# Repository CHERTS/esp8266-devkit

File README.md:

Unofficial Development Kit for Espressif ESP8266
================================================

[По-русски / In Russian](README.ru.md)

<b>Unofficial Development Kit for Espressif ESP8266</b> - this is an unofficial firmware development kit for SoC Espressif ESP8266.<br>

<b>The kit includes the following components and tools:</b><br>

1. Unofficial GCC compiler for SoC Xtensa LX106.<br>
2. Official Espressif ESP8266 SDK v2.0.0<br>
3. Documentation for SoC ESP8266.<br>
4. Examples in the firmware source code in C and С++ language.<br>
5. Additional tools for working with boards based on the ESP8266.<br>

<a href="http://programs74.ru/udkew-en.html">Official site of the project, where you can download the installer for Windows</a>

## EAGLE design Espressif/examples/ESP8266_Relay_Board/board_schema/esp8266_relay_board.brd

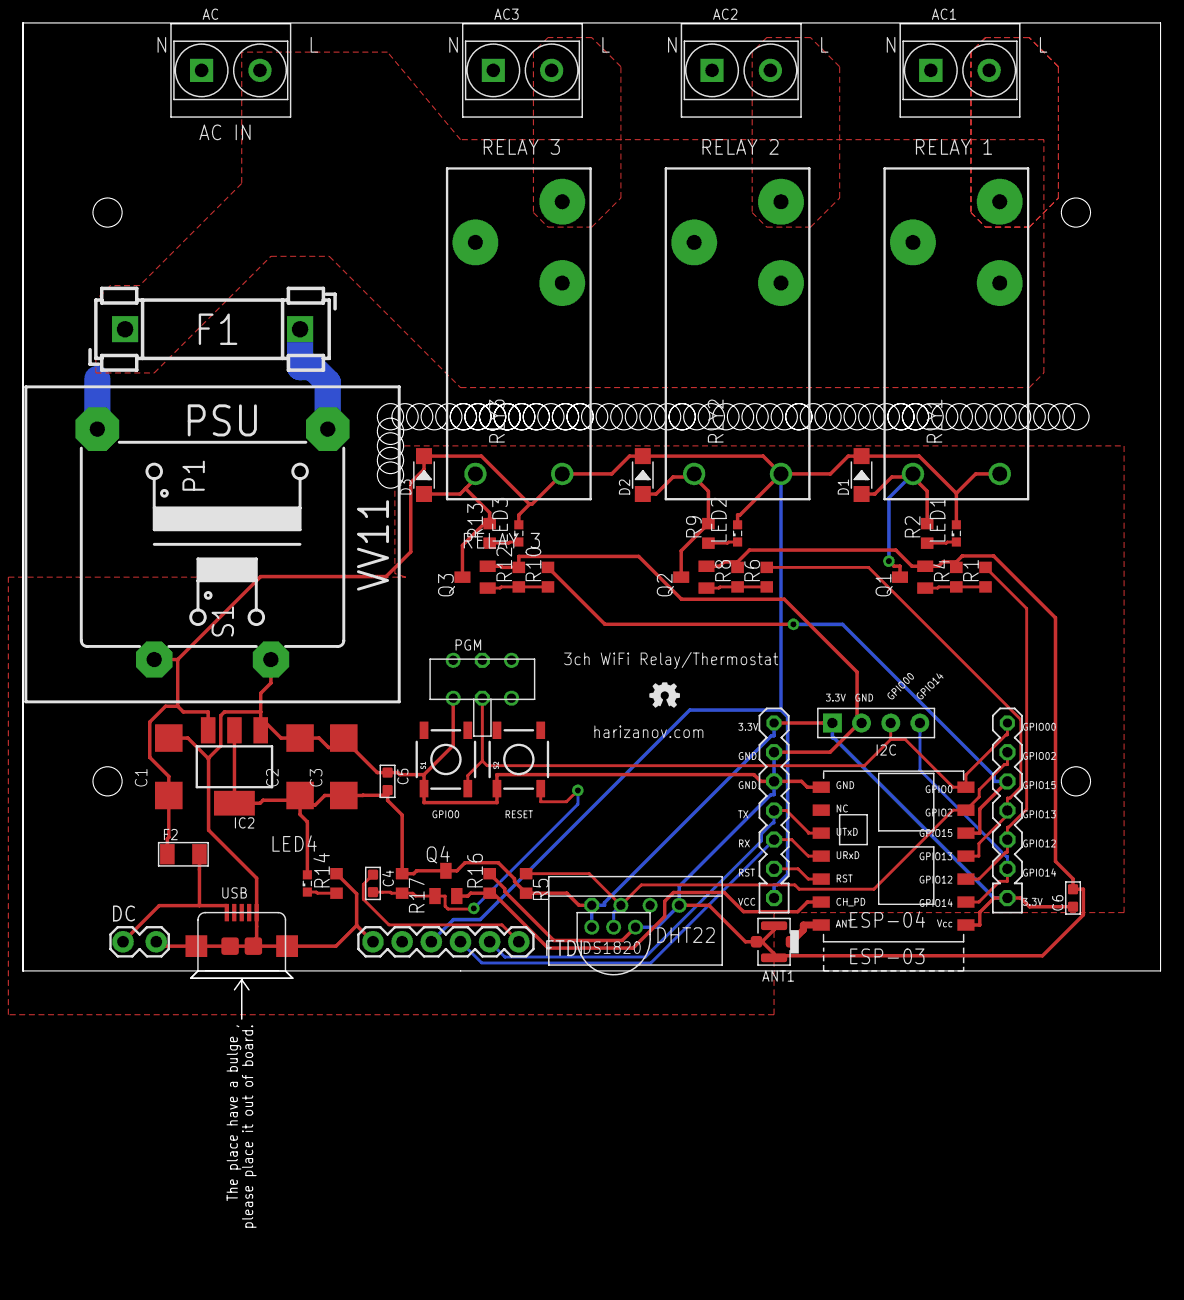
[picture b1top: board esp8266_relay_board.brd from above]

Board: 2 copper layers, 99.1 x 86.7 mm, 54 parts (0 on the bottom side), 33 nets.

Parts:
AC, AC1, AC2, AC3: 2P-5.0
ANT1: U-FL
C1: 10u/35V; SMC_C
C2, C3: 470uF/35V; SMC_C
C4, C5, C6: 100nF; C0603
D1, D2, D3: SOD-123
DC: 1X02_LOCK
DHT22: RHT03_DHT-22
ESP8266: ESP8266; ESP-04
F1: FUSE_HOLDER_5X20MM
F2: F1206
FTDI: FTDI_BASIC
I2C: 4P-2.54-65/35MIL
IC2: LM1117-IMP3.3; SOT223
LED1, LED2, LED3, LED4: SML0603
PGM: 6P-2CH-2.54-L9.0XW3.5XH3.2-90D
PORT5, PORT11: CON7PIN-PAD; PORT7PAD
PSU: VV11
Q1, Q2, Q3, Q4: 2N3904; SOT23
R1, R2, R6, R9, R10, R13, R14, R16: 330; R0603
R4, R8, R12: 3.3K; R0603
R5, R17: 10K; R0603
RLY1, RLY2, RLY3: RT-C/O12A3.5
S1, S2: !RESET; TACTILE_SWITCH_SMD
U$1: DS1820TO92; DS1820
USB: B-SMD-5P

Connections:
+3V3: C2.+, C3.+, C5.2, C6.1, DHT22.VDD, ESP8266.VCC, I2C.1, IC2.2, IC2.TER, LED4.A, PORT5.7, PORT11.1, Q4.3, R5.2, R17.1, U$1.VDD
CH_PD: ESP8266.CH_PD, Q4.2, R16.1
GND: ANT1.GND1, ANT1.GND2, ANT1.GND3, C1.-, C2.-, C3.-, C5.1, C6.2, DC.2, DHT22.GND, ESP8266.GND, FTDI.GND, I2C.2, IC2.1, PGM.CH1A, PORT5.5, PORT5.6, PSU.9, Q1.2, Q2.2, Q3.2, R4.2, R8.2, R12.2, R14.2, R16.2, S1.1, S2.1, U$1.GND, USB.5, USB.E1, USB.E2, USB.P1, USB.P2
GPIO0: ESP8266.GPIO0, I2C.3, PGM.COM1, PORT11.7, S1.3
GPIO2: DHT22.DATA, ESP8266.GPIO2, PORT11.6, R5.1, U$1.DQ
GPIO12: ESP8266.GPIO12, PORT11.3, R1.2
GPIO13: ESP8266.GPIO13, PORT11.4, R6.2
GPIO14: ESP8266.GPIO14, I2C.4, PORT11.2
GPIO15: ESP8266.GPIO15, PORT11.5, R10.2
GPIO16: ESP8266.GPIO18, PORT5.2
L: AC.2, F1.1, RLY1.11, RLY1.12, RLY2.11, RLY2.12, RLY3.11, RLY3.12
LOAD2: AC1.2, RLY1.14
LOAD22: AC2.2, RLY2.14
LOAD222: AC3.2, RLY3.14
N: AC.1, AC1.1, AC2.1, AC3.1, PSU.5
unnamed: Q1.1, R1.1, R4.1
unnamed: Q2.1, R6.1, R8.1
unnamed: LED2.C, R9.1
unnamed: D2.+, Q2.3, R9.2, RLY2.A2
unnamed: LED1.C, R2.1
unnamed: Q3.1, R10.1, R12.1
unnamed: LED3.C, R13.1
unnamed: D3.+, Q3.3, R13.2, RLY3.A2
unnamed: C4.1, FTDI.DTR
unnamed: F1.2, PSU.1
unnamed: LED4.C, R14.1
unnamed: ANT1.D, ESP8266.ANT
unnamed: D1.+, Q1.3, R2.2, RLY1.A2
unnamed: C4.2, Q4.1, R17.2, S2.3
RAW_VCC: DC.1, F2.2, USB.1
RX: ESP8266.UTXD, FTDI.RXI, PORT5.4
TX: ESP8266.URXD, FTDI.TXO, PORT5.3
VCC: C1.+, D1.-, D2.-, D3.-, F2.1, FTDI.VCC, IC2.3, LED1.A, LED2.A, LED3.A, PORT5.1, PSU.7, RLY1.A1, RLY2.A1, RLY3.A1

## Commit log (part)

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2015-04-05 Updated utils esptool-ck.exe
2015-04-05 Updated all Makefile
    All Makefile added option to specify the port speed utility esptool (ESPBAUD? = 115200)
2015-04-05 Updated inno installer script and changelog
2015-04-05 Updated example ESPWebFramework
2015-04-05 Updated changelog
2015-04-07 Updated example nodemcu-firmware
2015-04-07 Added example esp8266-ir-remote
    Infrared remote control library for ESP8266 RTOS SDK, original source https://github.com/valkuc/esp8266-ir-remote
2015-04-08 Updated xtensa-lx106-elf build script
2015-04-15 Updated example ESP8266_Relay_Board
2015-04-19 Updated Inno Setup script and changelog
2015-04-19 Updated example dht22_thingspeak
2015-04-26 Updated Espressif SDK v1.0.1 and documentation
2015-04-26 Added example hello_world_optimized (see readme_ru.txt)
2015-05-08 Updated libnet80211.a
2015-05-08 Added binary AT_v0.23_fix_sta_AP
2015-05-08 Moving firmware AT_v0.23_fix_sta_AP a folder bin/at
2015-05-08 Updated user_interface.h
2015-05-08 Updated documentation
2015-05-08 Updated example nodemcu-firmware Added display of information on the distribution of memory between sections firmware
2015-05-08 Updated compiler xtensa-lx106-gcc and xtensa-lx106-g++ Changed build option newlib, resulting in increased amount of free firmware IRAM. In the example "examples\nodemcu-firmware\" on the old compile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
2015-05-08 Updated Inno Setup script
2015-05-08 Updated ESP8266_RTOS_SDK
2015-05-08 Updated example esp_mqtt
2015-05-09 Updated utils
2015-05-09 Updated all Makefile and binary utils
2015-05-09 Updated example esp8266_ili9341
2015-05-09 Updated example esp8266_pcd8544
2015-05-09 Updated example esphttpd
2015-05-09 Updated example lwip_lib
2015-05-09 Updated example smart_config
2015-05-09 Added new documentation
2015-05-12 Updated utils esptool-ck.exe to version 0.4.3-2-g333f584
2015-05-13 Update Makefile
2015-05-13 Added command line build script
2015-05-14 Added command line mode
2015-05-14 Updated innosetup script
2015-05-14 Updated libs of Espressif SDK v1.0.1 (http://esp8266.ru/forum/attachments/lib_0514-zip.525/)
2015-05-15 Refactoring gpio16
    Was changed the methods with multiple returns.
2015-05-18 Updated utils esptool-ck.exe to version 0.4.4 + add flash size options for 8M, 16M, 32M * fix uploading with CH340
2015-05-21 Updated example sysinfo
2015-05-27 Update SDK v1.1.0 (folder ESP8266_SDK) SDK version 1.0.1 moved to a folder ESP8266_SDK_101;
2015-05-27 Patch based on SDK_v1.1.0
2015-05-27 Updated changelog and Inno setup script file
2015-05-27 sdk_patch_1.1.0: Add fix for force-requiring user_rf_pre_init()
2015-05-27 Fixed sdk_patch_1.1.0: Add fix for force-requiring user_rf_pre_init()
2015-05-27 Updated examples to be compatible with SDK 1.1.0
2015-05-27 Updated docs
2015-06-08 Update SDK v1.1.1 (folder ESP8266_SDK)
2015-06-08 Updated ESP8266_SDK\examples\driver_lib\
2015-06-08 Updated Inno setup file
2015-06-10 Fixed esptool.py - Fixed wrong size erase region for recording. - Fixed creation of superfluous segments for the loader, if the no data in segments rodata and etc. Patch by Viktor aka pvvx (https://g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
2015-06-10 Updated esptool.py - Add optional '--entry-symbol' option to override entry point symbol name Patch https://github.com/projectgus/esptool/commit/8ff0ee61a87dc03480a1cd89c8f22c185c81d619
2015-06-10 Updated esptool.py - Added patch: write_flash: Show actual flash write speed. https://github.com/pfalcon/esptool/commit/205608ba08b854bb16787e4f533e65ba1176f97a
2015-06-10 Updated esptool.py, fixed --entry-symbol
2015-06-10 Updated all examples
2015-06-10 Updated SDK v1.1.0 (folder ESP8266_SDK_110)
2015-06-11 Updated example dht22_thingspeak (fixed httpclient.c)
2015-06-16 Updated .gitignore
2015-06-16 * Update SDK v1.1.2 + Patch for scan issue based on SDK_v1.1.2 (folder ESP8266_SDK); * Updated documentation:
2015-06-16 Patch for scan issue based on SDK_v1.1.2
2015-06-19 Fixed example nodemcu-firmware
2015-07-01 Update build script (GCC 5.1)
2015-07-02 Updated all examples (compatible with GCC 5.1)
2015-07-02 Updated Makefile in example dht22_thingspeak
2015-07-02 Updated C++ examples
2015-07-02 Updated IoT_Demo example
2015-07-02 Updated example nodemcu-firmware; Updated changelog
2015-07-02 Updated esp_rtos_sdk_example example
2015-07-02 Updated esp8266-ir-remote/Makefile
2015-07-02 Remove example ESPWebFramework
2015-07-03 Updated Espressif SDK up to v1.2.0 (folder ESP8266_SDK)
2015-07-09 + Patch for SmartConfig based on SDK_v1.2.0 + Patch for SSL based on SDK_v1.2.0
2015-07-09 Updated esptool.py and libssl.a
2015-07-09 Updated esp_rtos_sdk_example
2015-07-09 Updated nodemcu-firmware
2015-07-13 Updated examples/smart_config
2015-07-14 Added SDRAM Optimization Patch for SDK_v1.2.0
2015-07-14 Fixed C++ examples, see http://www.esp8266.com/viewtopic.php?f=9&t=820&p=23253#p23253
2015-07-14 Fixed nodemcu-firmware (Thanks jcmvbkbc)
2015-07-15 Updated CPP LD file, see directory extra/ld/
2015-07-15 Fixed C++ examples, now ready Espressif SDK 1.2.0
2015-07-15 Updated all Makefile
2015-07-15 Updated esphttpd
2015-07-21 Updated all Makefile and esptool.py
2015-07-21 Updated esphttpd/Makefile
2015-08-03 Updated RTOS SDK
2015-08-03 Updated examples esp_rtos_sdk_example and esp_rtos_sdk_example_2
2015-08-03 Updated example esp_rtos_sdk_example_2
2015-08-08 * Update SDK v1.3.0 (folder ESP8266_SDK); * SDK version 1.2.0 moved to a folder ESP8266_SDK_120; * Updated documentation: - Delete files: 2A-ESP8266__IOT_SDK_User_Manual__EN_v1.1.0.pdf 2C-ESP8266__SD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
2015-08-24 Remove examples: lwip_lib; Added examples: lwip_open_demo_app;
2015-08-24 Updated lwip_open_demo_app
2015-08-24 Updated lwip_open_demo_app and changelog
2015-08-24 Updated libssl.a in Espressif SDK 1.3.0 (see http://bbs.espressif.com/viewtopic.php?f=46&t=925)
2015-08-24 Updated Espressif RTOS SDK v1.1.0 21.08.2015 (see http://bbs.espressif.com/viewtopic.php?f=46&t=986)
2015-08-24 Updated example lwip_open_demo_app
2015-08-24 + Added Espressif MESH SDK (beta) (folder ESP8266_MESH_SDK); + Added examples: esp_mesh_sdk_app_controller, esp_mesh_sdk_app_light, esp_mesh_sdk_app_switch;
2015-08-31 Updated Espressif RTOS SDK
2015-08-31 Added RTOS SDK Programming Guide EN v1.0.5
2015-08-31 Added ESP8266 Sleep Function Description EN v1.0
2015-08-31 Added ESP8266 Mesh User Guide EN v1.0
2015-08-31 Added libmgcc.a in ESP8266_MESH_SDK
2015-09-23 * Update Espressif SDK v1.4.0 (folder ESP8266_SDK); * Espressif SDK version 1.3.0 moved to a folder ESP8266_SDK_130; * Updated documentation: - Delete files: 2A-ESP8266__IOT_SDK_User_Manual__EN_v1.3.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
2015-09-28 Add example rboot-sampleproject from https://github.com/raburton/esp8266 commit 2de8bff7680e805d9b010e5af52f2bb5c9741e85.
2015-09-30 Adding the rboot files.
2015-10-04 Fixed rboot-sampleproject/.gitignore
2015-10-04 Fixed rboot-sampleproject
2015-11-01 Updated Espressif SDK v1.4.1 Pre5
2015-11-01 Updated gen_appbin.py
2015-11-01 Updated Espressif MESH SDK
2015-11-01 Updated changelog.txt
2015-11-02 Updated RTOS SDK v1.3.0
2015-11-02 Updated RTOS examples
2015-11-02 Updated nodemcu-firmware example
2015-11-02 Added example rBoot
2015-11-08 Updated at example;
2015-11-10 Added example SPI_slave;
2015-11-10 Added example I2S_Demo;
2015-11-19 Added file 3A_ESP8266_Flash_tool_user_manual_EN_v1.0.pdf
2015-11-19 Added example PWM_Demo;
2015-11-19 Updated example AT
2015-11-19 Added example UART_TCP_Passthrough_Demo;
2015-11-23 Update a utility "utils\esptool-ck.exe" to version 0.4.6-2
2015-11-29 SDK version 1.4.1 Pre5 moved to a folder ESP8266_SDK_141
2015-11-29 Updated example IoT_Demo
2015-12-01 Fixed esphttpd/Makefile
2015-12-01 Updated example esp_mesh_sdk_app_light
2015-12-01 Removing binaries
2015-12-01 Updated example esp_mesh_sdk_app_switch
2015-12-02 Updated documentations
2015-12-03 Fixed example lwip_open_demo_app
2015-12-03 Fixed example ESP8266_Relay_Board
2015-12-11 Updated example lwip_open_demo_app;
2015-12-28 * Documentation moved to a subfolder docs\ESP8266; * Examples moved to a subfolder examples\ESP8266;
2015-12-28 Updated python libs
2016-01-09 * Examples moved to a subfolder examples\ESP8266; * Utils moved to a subfolder utils\ESP8266;
2016-01-09 Added utils
2016-01-09 * Update SDK v1.5.1 (folder ESP8266_SDK);
2016-01-09 * SDK version 1.5.0 moved to a folder ESP8266_SDK_150;
2016-01-09 Updated standart Espressif examples at, smart_config, IoT_Demo
2016-01-09 Added standart Espressif examples wps
2016-02-11 * Update SDK v1.5.2 (folder ESP8266_SDK);
2016-02-11 * SDK version 1.5.1 moved to a folder ESP8266_SDK_151;
2016-02-11 * Updated documentation: - Delete files: 2C-ESP8266__SDK__Programming Guide__EN_v1.5.pdf + Added files: 2C-ESP8266__SDK__API Guide__EN_v1.5.2.pdf 2A_ESP8266_SDK Getting_Started_Guide_EN_v1.5_20151118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
2016-02-11 * Updated documentation: + Added files: 30A-ESP8266_NONOS_MESH_API_Reference_V1.0.0_20160203.pdf
2016-02-11 * Updated documentation: - Delete files: 30A_ESP8266__Mesh_User Guide__EN_v1.0.pdf + Added files: 30A-ESP8266__Mesh_User_Guide__EN_V1.2_20160203.pdf
2016-03-02 Updated esptool-ck.exe to version 0.4.8
2016-03-09 Update esphttpd examples
2016-03-09 Updated compiler build script
2016-03-09 Updated RTOS changelog
2016-03-09 Added Patch01 from SDK v1.5.2
2016-03-09 Added Patch01_AT_V0.60_on_ESP8266_NONOS_SDK_V1.5.2
2016-03-10 Fixed .gitignore
2016-03-10 Added compiler patches
2016-04-26 Update SDK v1.5.3 (folder ESP8266_SDK)
2016-04-26 SDK version 1.5.2 moved to a folder ESP8266_SDK_152
2016-05-08 Fixed esp_rtos_sdk_example
2016-05-14 Modifying the Admin check for the MinGw package installater
2016-05-23 Update SDK v1.5.4 (folder ESP8266_SDK)
2016-05-23 SDK version 1.5.3 moved to a folder ESP8266_SDK_153
2016-05-23 Update example lwip_open_demo_app
2016-05-23 Fixed RTOS examples
2016-05-23 Fixed example esp_mesh_sdk_app_controller
2016-05-23 Fixed example esp8266-ir-remote
2016-07-22 Added Espressif Documents link
2016-07-22 Update SDK v2.0.0 (folder ESP8266_SDK)
2016-07-22 SDK version 1.5.4 moved to a folder ESP8266_SDK_154
2016-07-22 Fixed boot loader version
2016-07-22 Updated command line tools (udkvars.bat)
2016-08-16 Added ESP8266_NONOS_SDK_V2.0.0_patch
2016-08-16 Updated ESP8266_RTOS_SDK (master)
2016-08-16 Updated ESP8266_RTOS_SDK_v1.4.2 Patch
2016-08-17 Update changelog
2016-08-22 - Deleted examples: esp_mesh_sdk_app_controller; esp_mesh_sdk_app_light; esp_mesh_sdk_app_switch;
2016-08-23 Updated the compiler xtensa-lx106-gcc and xtensa-lx106-g++ (added patches from jcmvbkbc to implement -fstack-usage and -Wstack-usage and -mlongcalls);
2016-08-27 Added esp8266_faq_en.pdf
2016-09-02 Fixed unziping xtensa_include.zip
2016-09-02 Fixed build-xtensa-lx106-elf.sh
2016-09-03 Updated install-mingw-package.bat and utils
2016-09-05 Added ESP12E pin configuration and function image
2016-09-08 Fixed py2exe scripts
2016-09-08 Added patch of GDB 7.11
2016-09-21 Updated py2exe script and python lib
2016-10-18 Update extra include
2016-10-18 Upgrade Makefile in all examples
2016-10-18 Update Inno setup file
2016-10-19 Updated CPP ld file
2016-10-19 Added common_nonos_app.mk file to implement the build of standard Espressif SDK firmware firmware containing APP directory)
2016-10-19 Fixed common_nonos_app.mk
2016-10-19 Added Espressif examples (repo https://github.com/espressif/esp8266-nonos-sample-code)
2016-10-24 Updated esptool
2016-10-28 Fixed utils
2016-10-28 Fixed mingw
2016-10-29 Updated utility esptool.exe and library.zip (pyserial for WinXP fix - https://goo.gl/agn8zu) for compatibility with WindowsXP;
2016-10-31 Fixed Inno Setup script
2016-11-05 Fixed example dht22_thingspeak
2016-11-05 Fixed example sysinfo
2016-11-08 Updated esptool.py
2016-11-08 Updated esptool-build.py
2016-11-08 Updated esptool.exe
2016-11-08 Fixed incorrect memory setting
2016-11-08 Convertin changelog_ru.txt to utf-8
2017-01-30 Fixed RTOS eagle.irom0text.bin address
2017-03-31 Fixed flash size arguments in megabits (esptool.py)
2017-04-21 Update RTOS SDK v1.5.0 (folder ESP8266_RTOS_SDK)
2017-04-21 + Removing old RTOS_SDK examples and adding new * Fixed gen_appbin.exe
2017-04-21 Fixed common_rtos.mk
2017-04-23 Revert gen_appbin
2017-04-23 Revert common_*.mk
2017-05-18 Update RTOS SDK up to v1.5.0-dev(7f7a714)
2017-05-18 Update SDK v2.1.0 (folder ESP8266_SDK);
2017-05-18 Update Inno setup script
2017-05-18 Fixed examples
2017-05-30 Update RTOS_SDK
2017-07-11 Updated RTOS SDK up to 1.5.0-dev(c27334ca) and NONOS SDK up to git-89ba08ee
2017-11-13 Upgrade ESP8266_RTOS_SDK to the latest version from git

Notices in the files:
parts and their libraries:
SparkFun-Connectors: Licensing: CC v3.0 Share-Alike You are welcome to use this library for commercial purposes.
